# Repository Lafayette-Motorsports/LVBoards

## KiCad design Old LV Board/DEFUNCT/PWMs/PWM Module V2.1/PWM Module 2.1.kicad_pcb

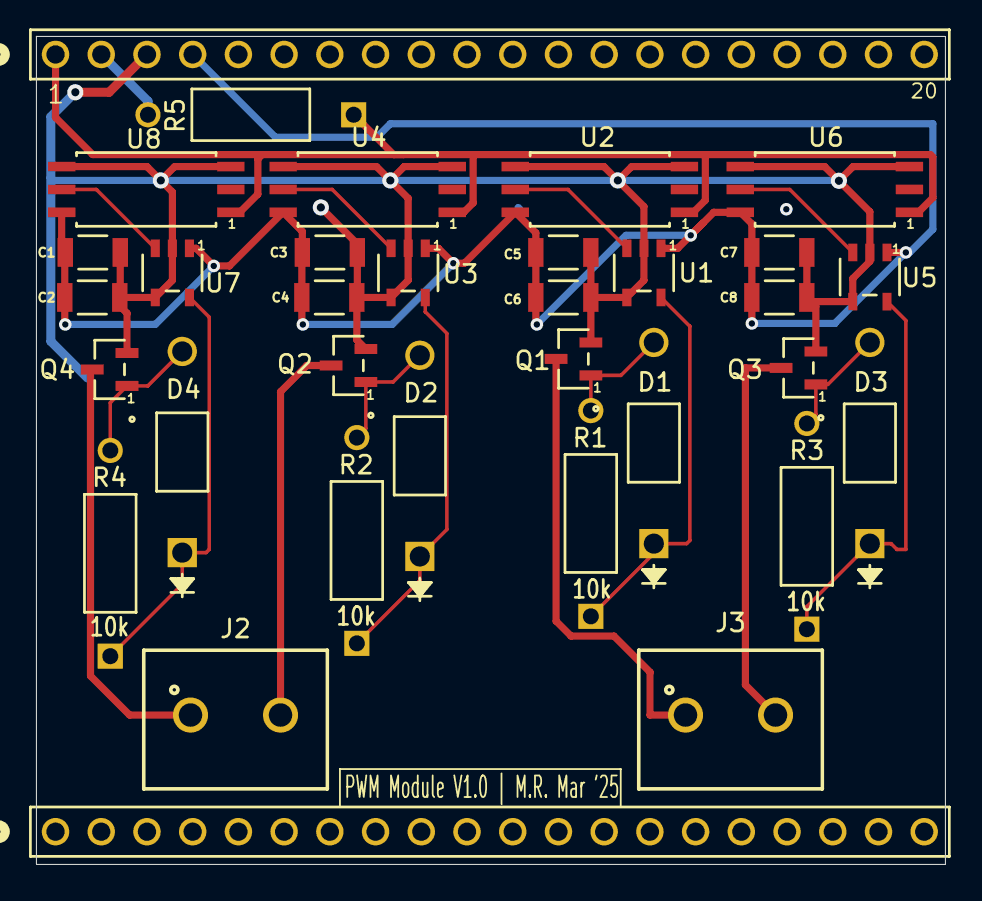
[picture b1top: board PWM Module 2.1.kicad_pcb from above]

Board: 2 copper layers, 50.5 x 46.0 mm, 33 parts (0 on the bottom side), 20 nets.

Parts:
C1, C2, C3, C4, C5, C6, C7, C8: 0.1u; CAP_CL31_SAM
D1, D2, D3, D4: 1N4001; DO-41_DIO
J2, J3: Conn_01x02_Pin; 691137710002
J5, J5#2: PH1-20-UA; CONN_PH1-20-UA_ADM
Q1, Q2, Q3, Q4: DMN3404L-7; SOT23_DIO
R1, R2, R3, R4, R5: 10k; STA_CF14_STP
U1, U3, U5, U7: UCC27517DBVR; DBV5_TEX
U2, U4, U6, U8: TLP2745TP_E; SO6L_TOS

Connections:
5V+: J5.1, R5.1, U2.1, U4.1, U6.1, U8.1
12V+: C1.1, C2.1, C3.1, C4.1, C5.1, C6.1, C7.1, C8.1, J5.4, U1.1 (VDD), U2.6, U3.1 (VDD), U4.6, U5.1 (VDD), U6.6, U7.1 (VDD), U8.6
GND: C1.2, C2.2, C3.2, C4.2, C5.2, C6.2, C7.2, C8.2, J5.3, Q1.2 (S), Q2.2 (S), Q3.2 (S), Q4.2 (S), U1.2 (GND), U1.4 (IN-), U2.3, U2.4, U3.2 (GND), U3.4 (IN-), U4.3, U4.4, U5.2 (GND), U5.4 (IN-), U6.3, U6.4, U7.2 (GND), U7.4 (IN-), U8.3, U8.4
unnamed: D1.2 (A), Q1.1 (G), R1.2
unnamed: D1.1 (K), R1.1, U1.5 (OUT)
unnamed: D2.2 (A), Q2.1 (G), R2.2
unnamed: D2.1 (K), R2.1, U3.5 (OUT)
unnamed: D3.2 (A), Q3.1 (G), R3.2
unnamed: D3.1 (K), R3.1, U5.5 (OUT)
unnamed: D4.2 (A), Q4.1 (G), R4.2
unnamed: D4.1 (K), R4.1, U7.5 (OUT)
unnamed: J2.1, Q4.3 (D)
unnamed: J2.2, Q2.3 (D)
unnamed: J3.1, Q1.3 (D)
unnamed: J3.2, Q3.3 (D)
unnamed: U1.3 (IN+), U2.5
unnamed: U3.3 (IN+), U4.5
unnamed: U5.3 (IN+), U6.5
unnamed: U7.3 (IN+), U8.5
VPWM: J5.2, R5.2

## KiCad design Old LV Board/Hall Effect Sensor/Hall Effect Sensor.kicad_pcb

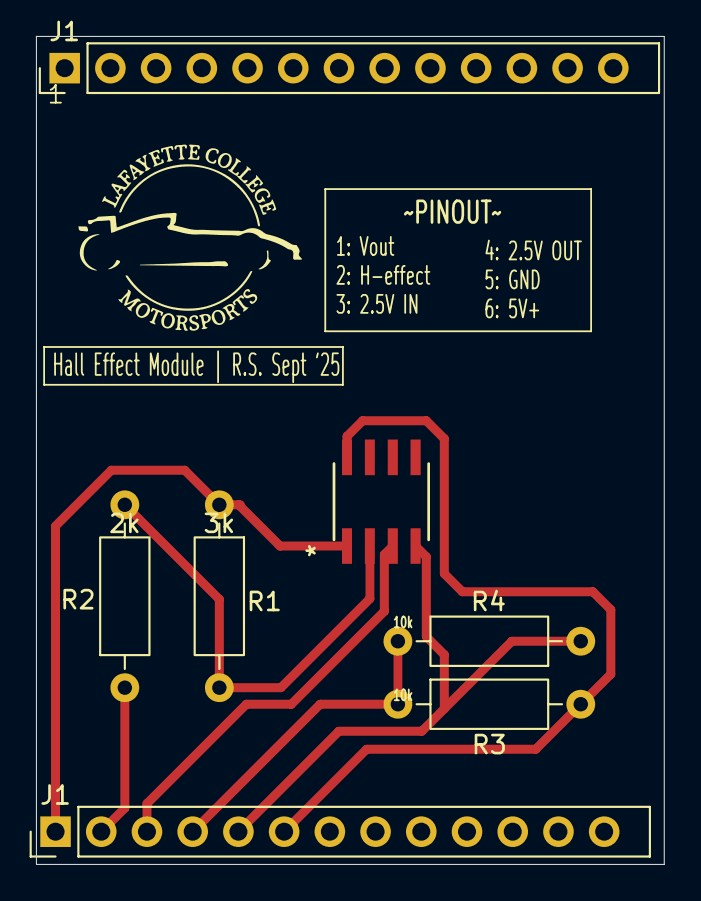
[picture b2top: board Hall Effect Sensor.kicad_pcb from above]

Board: 2 copper layers, 34.9 x 46.0 mm, 7 parts (0 on the bottom side), 7 nets.

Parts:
J1, J1#2: PH1-20-UA; PinHeader_1x20_P2.54mm_Vertical
R1: 3k; R_Axial_DIN0207_L6.3mm_D2.5mm_P10.16mm_Horizontal
R2: 2k; R_Axial_DIN0207_L6.3mm_D2.5mm_P10.16mm_Horizontal
R3, R4: 10k; R_Axial_DIN0207_L6.3mm_D2.5mm_P10.16mm_Horizontal
opamp1: ADA4510-2ARZ; R-8_ADI

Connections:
+5V in: J1#2.6, R3.2, opamp1.8 (V+)
GND: J1#2.5, R4.1, opamp1.4 (V-)
Hall Effect Out: J1#2.2, R2.1
unnamed: R1.2, R2.2, opamp1.2 (INA-)
V(2.5)OUT: J1#2.4, R3.1, R4.2
V(2.5V)IN: J1#2.3, opamp1.3 (INA+)
Vout+: J1#2.1, R1.1, opamp1.1 (OUTA)

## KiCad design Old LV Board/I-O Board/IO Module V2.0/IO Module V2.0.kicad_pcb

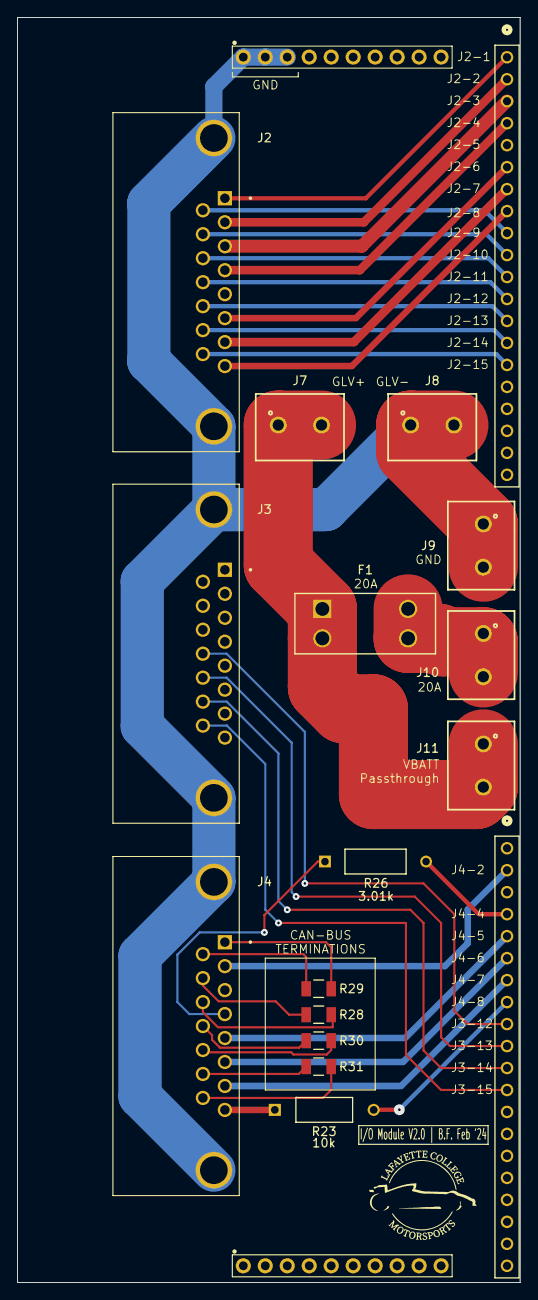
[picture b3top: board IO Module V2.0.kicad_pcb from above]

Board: 2 copper layers, 58.1 x 146.2 mm, 18 parts (0 on the bottom side), 36 nets.

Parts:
F1: 20A; 3568_KEY
J1: PH1-10-UA; 1X10-2.54MM-THT
J2, J3, J4: *; AMPHENOL_L717SDA15P1ACH4F
J5, J6: 20-0600-21; CONN_20-0600-21_ARS
J7, J8, J9, J10, J11: 691137710002
R23: 10k; STA_CF14_STP
R26: 3.01k; YAG_MF25_YAG
R28, R29, R30, R31: 120; RES_TNPW1206_VIS

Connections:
unnamed: F1.1, F1.2, J7.1, J7.2, J11.1, J11.2
unnamed: F1.3, F1.4, J10.1, J10.2
unnamed: J1.1, J1.2, J1.3, J2.S1 (SHIELD), J2.S2 (SHIELD), J3.S1 (SHIELD), J3.S2 (SHIELD), J4.S1 (SHIELD), J4.S2 (SHIELD), J8.1, J8.2, J9.1, J9.2
unnamed: J2.01, J5.1
unnamed: J2.02, J5.2
unnamed: J2.03, J5.3
unnamed: J2.04, J5.4
unnamed: J2.06, J5.6
unnamed: J2.07, J5.7
unnamed: J2.08, J5.8
unnamed: J2.09, J5.9
unnamed: J2.10, J5.10
unnamed: J2.11, J5.11
unnamed: J2.12, J5.12
unnamed: J2.13, J5.13
unnamed: J2.14, J5.14
unnamed: J2.15, J5.15
unnamed: J3.12, J6.9
unnamed: J3.13, J6.10
unnamed: J3.14, J6.11
unnamed: J3.15, J6.12
unnamed: J4.01, R29.1
unnamed: J4.04, R26.1
unnamed: J4.05, J6.5
unnamed: J4.06, J6.6
unnamed: J4.07, J6.7
unnamed: J4.08, R23.1
unnamed: J4.09, R29.2
unnamed: J4.10, R28.1
unnamed: J4.11, R28.2
unnamed: J4.12, R30.1
unnamed: J4.13, R30.2
unnamed: J4.14, R31.1
unnamed: J4.15, R31.2
unnamed: J6.4, R26.2
unnamed: J6.8, R23.2

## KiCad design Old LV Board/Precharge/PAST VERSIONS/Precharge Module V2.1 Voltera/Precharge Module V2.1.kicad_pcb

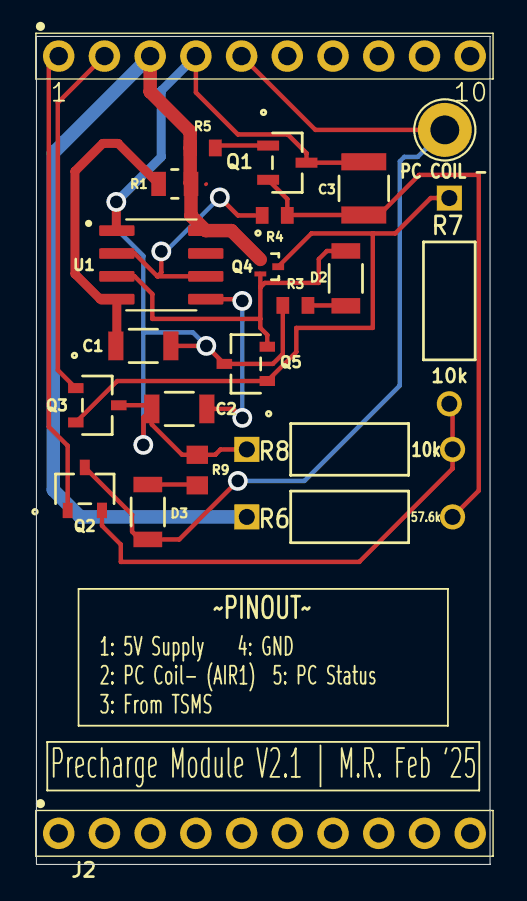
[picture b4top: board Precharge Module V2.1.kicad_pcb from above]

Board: 2 copper layers, 25.2 x 46.0 mm, 22 parts (0 on the bottom side), 15 nets.

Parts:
C1, C2: 0.1u; CAP_CL31_SAM
C3: 47u; CAP_CL32_SAM
D2: 3 second timer; LED_AP3216SYD_KNB
D3: LED (Test); LED_AP3216SYD_KNB
J1, J2: PH1-10-UA; 1X10-2.54MM-THT
PC COIL -: TestPoint; TestPoint_Loop_D2.60mm_Drill1.6mm_Beaded
Q1: SS8550; SOT-23_MCC
Q2, Q3, Q5: NMOS; SOT23_INF
Q4: PMOS; VESM_TOS
R1: 22k; STA_RMCF0805_STP
R3, R4, R5: 1k; STA_RMCF0603_STP
R6: 57.6k; STA_CF14_STP
R7, R8: 10k; STA_CF14_STP
R9: 150R; RC0805N_YAG
U1: NE555D; SOIC127P599X175-8N

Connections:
unnamed: D2.2 (A), Q4.2 (G), Q5.2 (G), U1.3 (Q)
unnamed: D2.1 (K), R3.1
unnamed: D3.2 (A), J1.5, PC COIL -.1, Q2.3 (S)
unnamed: D3.1 (K), R9.2
unnamed: Q1.1 (B), R5.2
unnamed: C1.2, C2.2, C3.2, J1.4, Q1.3 (C), Q3.3 (S), Q5.3 (S), R3.2, R8.1, R9.1, U1.1 (GND)
unnamed: C3.1, Q1.2 (E), R4.2, R6.2
unnamed: J1.1, Q2.1 (D)
unnamed: Q2.2 (G), R7.2, R8.2
unnamed: J1.2, Q3.1 (D)
unnamed: Q3.2 (G), Q4.3 (S), Q5.1 (D), R7.1
unnamed: J1.3, Q4.1 (D), R1.2, R5.1, R6.1, U1.8 (VCC)
unnamed: C2.1, U1.5 (CV)
unnamed: C1.1, R1.1, U1.4 (R)
unnamed: R4.1, U1.2 (TR), U1.6 (THR)

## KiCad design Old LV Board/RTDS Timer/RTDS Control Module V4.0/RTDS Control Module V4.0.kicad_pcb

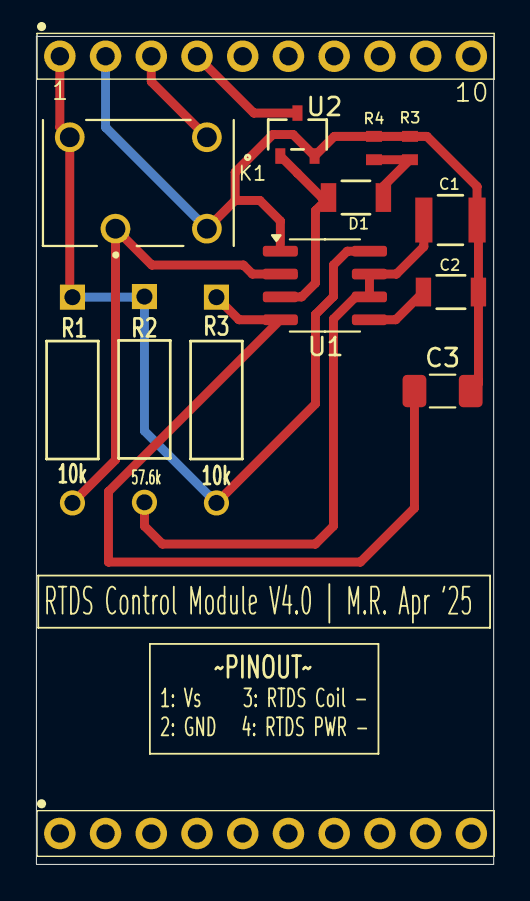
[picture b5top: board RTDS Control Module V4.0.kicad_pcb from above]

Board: 2 copper layers, 25.4 x 46.0 mm, 14 parts (0 on the bottom side), 10 nets.

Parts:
C1: 47u; CAP_CL32_SAM
C2: 0.1u; CAP_CL31_SAM
C3: 10u; C_1206_3216Metric_Pad1.33x1.80mm_HandSolder
D1: LED (Test); LED_AP3216SYD_KNB
J1, J2: PH1-10-UA; 1X10-2.54MM-THT
K1: G6L-1P_DC5; RELAY_G6L-1P_DC5
R1, R3#2: 10k; STA_CF14_STP
R2: 57.6k; STA_CF14_STP
R3, R4: 1k; STA_RMCF0603_STP-L
U1: NE555D; SOIC-8_3.9x4.9mm_P1.27mm
U2: IRLML2060TRPBF; SOT23_INF

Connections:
unnamed: D1.2 (A), U1.3 (Q), U2.1 (G)
unnamed: D1.1 (K), R3.1, R4.1
unnamed: J1.3, K1.5
unnamed: C2.1, U1.5 (CV)
unnamed: C1.1, R2.2, U1.6 (THR), U1.7 (DIS)
unnamed: C1.2, C2.2, C3.2, J1.2, K1.4, R3.2, R4.2, U1.1 (GND), U2.2 (S)
unnamed: J1.1, K1.8, R1.1, R2.1, R3#2.2, U1.8 (VCC)
unnamed: K1.2, R1.2, U1.2 (TR)
unnamed: J1.4, U2.3 (D)
RESET: C3.1, R3#2.1, U1.4 (R)

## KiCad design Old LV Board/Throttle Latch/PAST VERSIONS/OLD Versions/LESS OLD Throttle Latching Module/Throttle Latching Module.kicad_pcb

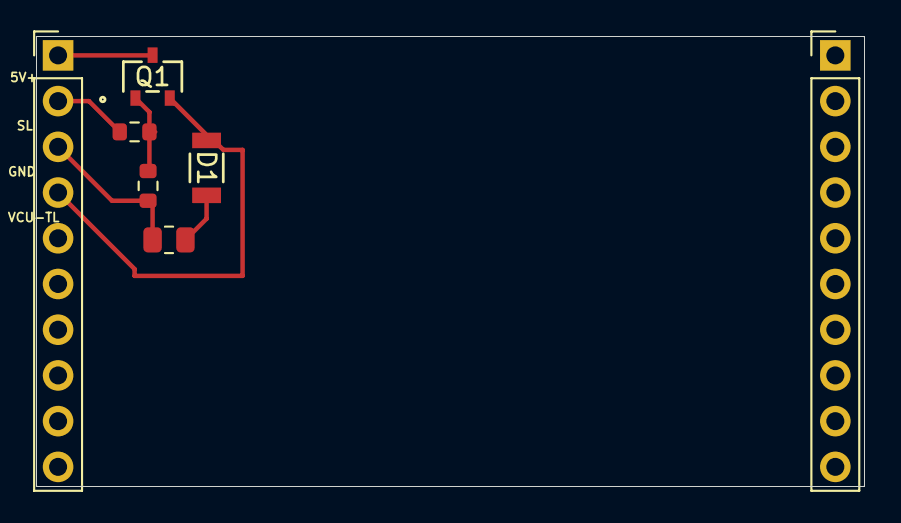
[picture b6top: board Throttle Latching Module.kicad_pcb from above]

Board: 2 copper layers, 46.0 x 25.0 mm, 7 parts (0 on the bottom side), 5 nets.

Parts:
D1: LED (Test); LED_AP3216SYD_KNB
J1, J1#2: PH1-10-UA; PinHeader_1x10_P2.54mm_Vertical
Q1: AON6411; SOT23_INF
R1: 150R; R_0805_2012Metric
R2, R3: 10k; R_0603_1608Metric

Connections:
unnamed: D1.2 (A), J1.4, Q1.1 (S), Q1.2 (S), Q1.3 (S)
unnamed: D1.1 (K), R1.2
unnamed: J1.2, R2.1
unnamed: J1.3, R1.1, R3.1
unnamed: R2.2, R3.2
